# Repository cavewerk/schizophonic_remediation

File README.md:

# schizophonic_remediation
Documentation and patch repository for alternative modes of transduction

> **Moved.** This work continues as *la harpe Éliane* at
> [github.com/cavewerk/la-harpe-eliane](https://github.com/cavewerk/la-harpe-eliane),
> which includes this repository's full history. This repo is archived.

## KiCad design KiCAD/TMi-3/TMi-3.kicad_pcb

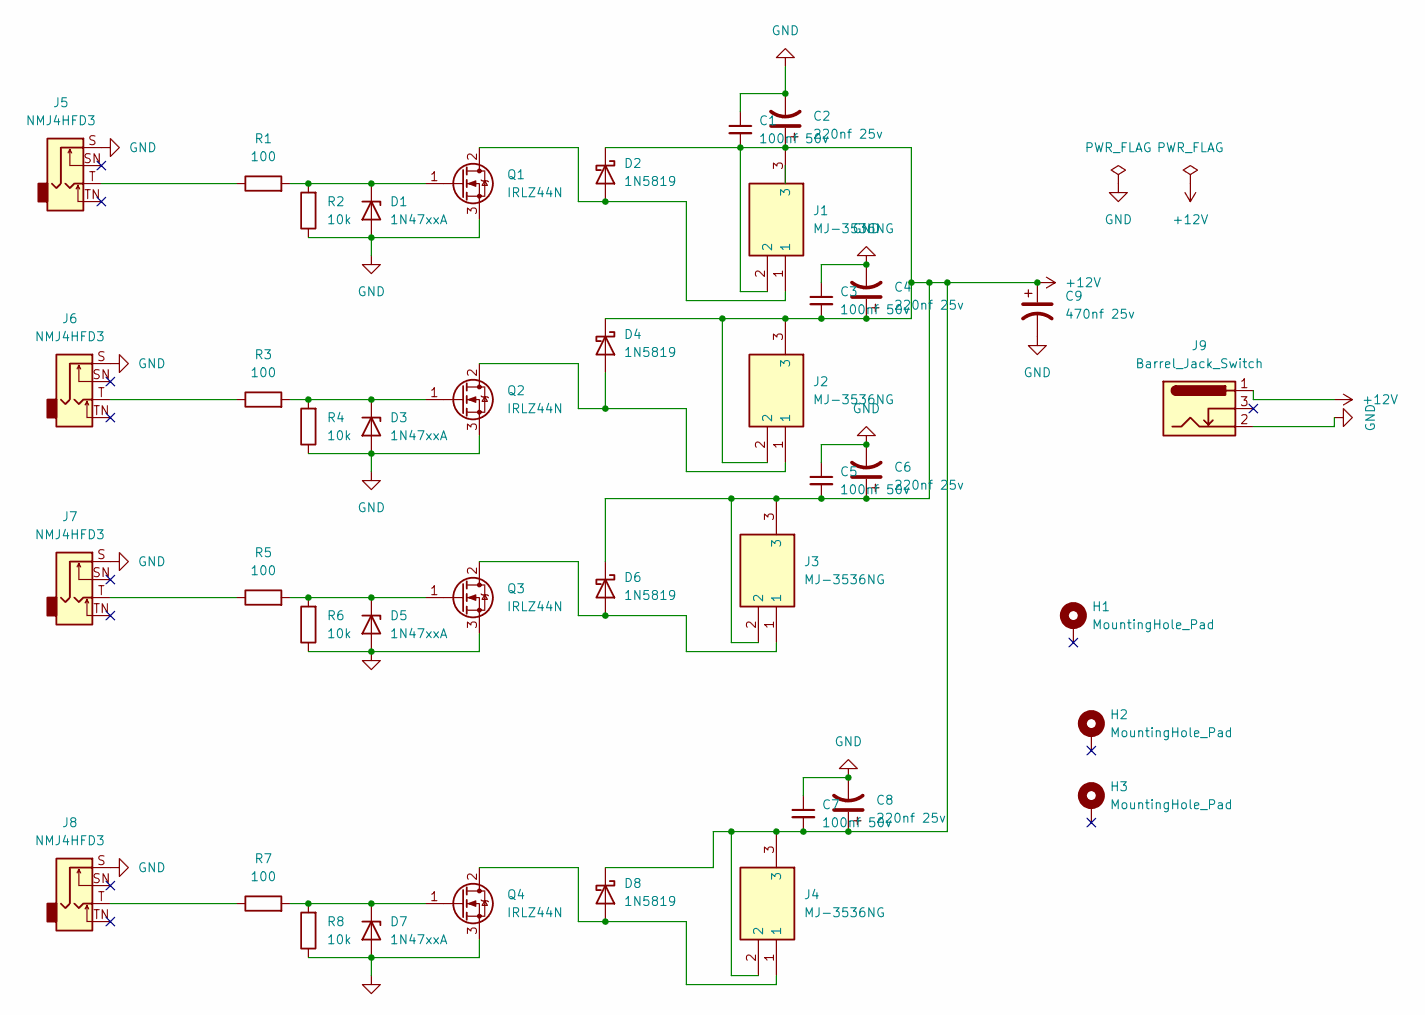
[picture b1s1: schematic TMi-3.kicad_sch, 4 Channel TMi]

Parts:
C1, C3, C5, C7: 100nf 50v; C_0805_2012Metric_Pad1.18x1.45mm_HandSolder
C2, C4, C6, C8: 220nf 25v; CP_Radial_D8.0mm_P3.50mm
C9: 470nf 25v; CP_Radial_D10.0mm_P5.00mm
D1, D3, D5, D7: 1N47xxA; D_DO-41_SOD81_P10.16mm_Horizontal
D2, D4, D6, D8: 1N5819; D_DO-41_SOD81_P10.16mm_Horizontal
H1, H2, H3: MountingHole_Pad; MountingHole_2.2mm_M2_DIN965_Pad_TopBottom
J1, J2, J3, J4: MJ-3536NG; MJ3536NG_Tighter_Pads; Mouser Part Number 490-MJ-3536NG
J5, J6, J7, J8: NMJ4HFD3; Jack_6.35mm_Neutrik_NMJ4HFD3_Horizontal
J9: Barrel_Jack_Switch; BarrelJack_Horizontal
Q1, Q2, Q3, Q4: IRLZ44N; TO-220-3_Vertical
R1, R3, R5, R7: 100; R_1206_3216Metric_Pad1.30x1.75mm_HandSolder
R2, R4, R6, R8: 10k; R_1206_3216Metric_Pad1.30x1.75mm_HandSolder

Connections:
+12V: C1.2, C2.1, C3.2, C4.1, C5.2, C6.1, C7.2, C8.1, C9.1, D2.1 (K), D4.1 (K), D6.1 (K), D8.1 (K), J1.2, J1.3, J2.2, J2.3, J3.2, J3.3, J4.2, J4.3, J9.1
GND: C1.1, C2.2, C3.1, C4.2, C5.1, C6.2, C7.1, C8.2, C9.2, D1.2 (A), D3.2 (A), D5.2 (A), D7.2 (A), J5.S, J6.S, J7.S, J8.S, J9.2, Q1.3 (S), Q2.3 (S), Q3.3 (S), Q4.3 (S), R2.1, R4.1, R6.1, R8.1
unnamed: D1.1 (K), Q1.1 (G), R1.2, R2.2
unnamed: D2.2 (A), J1.1, Q1.2 (D)
unnamed: D3.1 (K), Q2.1 (G), R3.2, R4.2
unnamed: D4.2 (A), J2.1, Q2.2 (D)
unnamed: D5.1 (K), Q3.1 (G), R5.2, R6.2
unnamed: D6.2 (A), J3.1, Q3.2 (D)
unnamed: D7.1 (K), Q4.1 (G), R7.2, R8.2
unnamed: D8.2 (A), J4.1, Q4.2 (D)
unnamed: J5.T, R1.1
unnamed: J6.T, R3.1
unnamed: J7.T, R5.1
unnamed: J8.T, R7.1

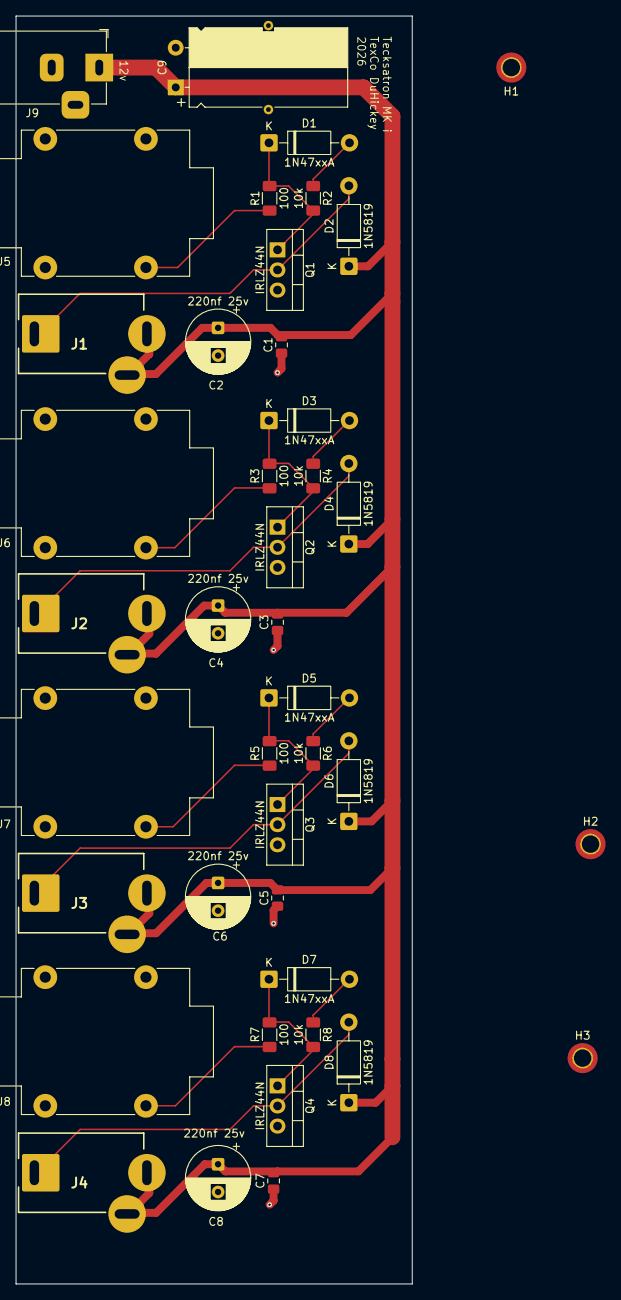
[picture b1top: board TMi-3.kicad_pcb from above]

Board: 2 copper layers, 50.0 x 160.0 mm, 41 parts (0 on the bottom side), 14 nets.

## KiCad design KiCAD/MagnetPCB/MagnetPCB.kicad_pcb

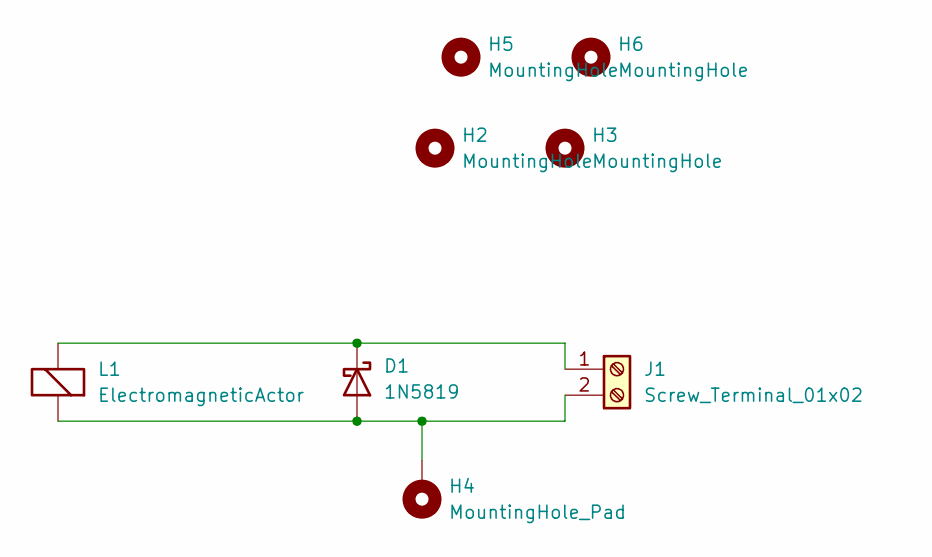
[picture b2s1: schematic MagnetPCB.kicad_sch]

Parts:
D1: 1N5819; D_DO-41_SOD81_P10.16mm_Horizontal
H2, H3, H5, H6: MountingHole; MountingHole_2.2mm_M2
H4: MountingHole_Pad; MountingHole_4.3mm_M4_Pad
J1: Screw_Terminal_01x02; TerminalBlock_RND_205-00045_1x02_P5.00mm_Horizontal
L1: ElectromagneticActor; L_Radial_D21.0mm_P19.00mm

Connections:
unnamed: D1.2 (A), H4.1 (1_1), J1.2, L1.1 (-)
unnamed: D1.1 (K), J1.1, L1.2 (+)

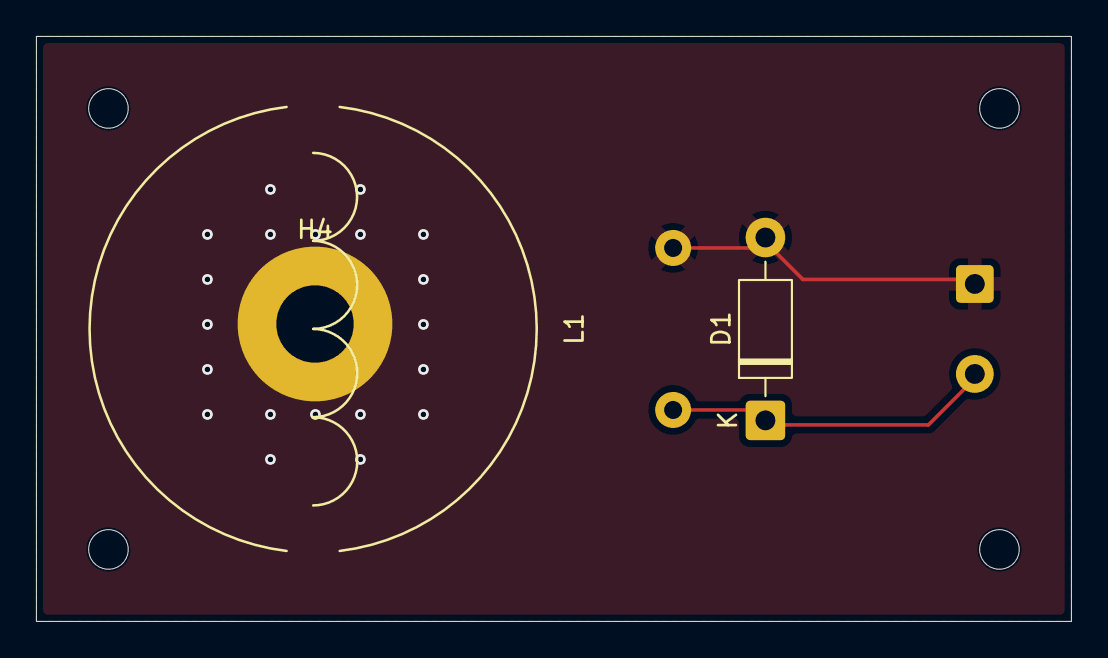
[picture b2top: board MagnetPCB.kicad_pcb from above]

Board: 2 copper layers, 57.5 x 32.5 mm, 8 parts (1 on the bottom side), 2 nets.

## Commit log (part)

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2025-12-30 Add Vault
    Rather than just a reflection journal, I am incorporating my full notes structure into my documentation to support the making as well as the writing.
2025-12-30 First Demo
    So the circuit is working! No shorts and very stable. Uploaded video targeting different harmonics.
2026-01-06 Journal Update
    Swap to arduino mega
    Add sample/hold button workaround to get stable pot readings
2026-01-08 Control and Performance
    - Stabilize interface
    - Swap out buttons for capacitive sensor (less noise on recordings)
    - Add two performances to journal
2026-01-16 mostly writing
    Journal entries, essay ideas and naming ideas.
2026-01-27 Journal Entries
    Lots of journal entries
2026-01-30 Adding tags
2026-02-08 AdditiveSynth Patch
    # Additive Synth
    New Max patch for driving the magnet. No more arduino for now. Very messy, not optimized, but sounding doooooopppppppe
2026-03-02 Build 1.0
    # Max patch
    Big build:
    - Additive synth with fader control over OSC
    - Sequencer
    # Touch OSC patch
    - Faders
2026-03-02 Messed up save
    - Additive1 is main
2026-03-02 Responsive TouchOSC UI
    Harmonic multiplier is displayed in touch osc patch
2026-03-02 Oops
    Didn't save touch osc patch
2026-03-04 Defining texatron mk i
    Offered a definition of this prototype in journal entry
2026-03-28 Main
    Main I complete
2026-04-11 MC
    Added MC patch
